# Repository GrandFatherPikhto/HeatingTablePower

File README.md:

# Reflow Oven & Heating Table Power Board (Dual Triac Switch)

*Читать на русском: [README_ru.md](README_ru.md)*

Hardware design (KiCad schematic and PCB layout) for the mains-side power board of the dual-channel reflow oven / heating table controller ([`../ControllerSTM32F103C8T6`](../ControllerSTM32F103C8T6)).

The board switches two resistive heaters from 220 V AC with **BTA12-600CRG** triacs. Each triac is driven through a **MOC3063M** zero-crossing optotriac, so the logic side is galvanically isolated from the mains.

---

## Key Features & Hardware Architecture

* **Two identical heater channels:** one hierarchical sheet (`channel.kicad_sch`) is placed twice, as `Channel 1` and `Channel 2`. Each channel has:
  * a BTA12-600CRG triac (`Q1` / `Q2`; 12 A RMS, 600 V, TO-220, insulated tab);
  * a MOC3063M optotriac (`U2` / `U3`) with a 330 Ω gate resistor (`R9` / `R12`, 1210);
  * an RC snubber across the triac: 39 Ω (`R10` / `R13`, axial) + 0.1 µF 630 V (`C7` / `C8`);
  * a heater output terminal (`J6` / `J7`).

  On the PCB, channel 2 is the channel 1 layout shifted 20 mm to the right.
* **Zero-cross switching:** the optotriacs turn the triacs on only near the mains zero crossing. This reduces inrush current and EMI. It also means the outputs suit on/off or burst-fire (whole half-cycle) control, not phase-angle dimming.
* **Logic input:** the control inputs come from `J4` and accept 3.3 V or 5 V logic. Each passes a 1 kΩ series resistor (`R3`, `R4`) into a Schmitt-trigger inverter `U1`, which must be a **74HCT14** (see note 5). Each input has a 10 kΩ pull-down (`R1`, `R2`), so a disconnected cable means "heater off".
* **Optotriac drive:** the LED of each MOC3063M is fed from `+5P` through 330 Ω (`R8`, `R11`) and is sunk by the `U1` output, giving ≈ 10–11 mA (the MOC3063M needs 5 mA max to trigger).
* **Status LEDs:** a second inverter of `U1` in each channel drives the channel LED, which is lit while the heater is on:
  * `D2` (purple, `R6`) — channel 1;
  * `D1` (blue, `R5`) — channel 2;
  * `D3` (red, `R7`) — logic power present.
* **Net ties `NT1` / `NT2`:** they split the thin optotriac branch (`UP_ARM`, 0.5 mm track) off the heavy heater net (`220V_UP`). The branch is therefore a separate net with its own width, and the mains-track rule in `Power.kicad_dru` does not apply to it.
* **Mains input protection:** varistor `RV1` (SIOV-S14K275, 275 V AC) and an across-the-line capacitor `C1` (0.1 µF 630 V). **There is no fuse on the board** — see the notes.
* **Logic supply filtering:** `C4` (47 µF 10 V), `C5` (10 µF) and `C6` (100 nF) at `J5`; `C2` (100 nF) and `C3` (10 µF) at `U1`.
* **Board:** 2 layers, ≈ 93 × 65 mm, 4× M3 mounting holes.

---

## Repository Structure

* `Power.kicad_pro` — KiCad project file.
* `Power.kicad_sch` — root schematic sheet. Its hierarchical sheets:
  * `signal.kicad_sch` (`Signal`) — `J4`, the input network, `U1` and the channel LEDs;
  * `power.kicad_sch` (`Power`) — `J5`, logic supply filtering and the power LED;
  * `220v_in.kicad_sch` (`220V`) — `J1`, `RV1`, `C1`;
  * `channel.kicad_sch` (`Channel 1`, `Channel 2`) — one heater channel.
* `Power.kicad_pcb` — PCB layout.
* `Power.kicad_dru` — Custom design rule: tracks of the mains nets (`*/220V*`) may have exposed copper (no solder mask) so they can be tinned for extra current capacity.
* `gerber/` — Gerber and drill files. They are dated 27.10 and belong to the previous, flat-schematic revision. Regenerate them before ordering.
* `out/` — BOM and netclass audit reports.

---

## Connector Pinouts

### J1 — Mains Input (`220V In`, Phoenix MKDS 1.5, 5.08 mm)

| Pin | Signal | Description |
| :---: | :--- | :--- |
| 1 | `/220V` | Goes to A1 of both triacs, the snubbers, `RV1` and `C1`. Connect **Line (L)** here. |
| 2 | `/220V_COMMON` | Goes straight to pin 2 of both heater terminals. Connect **Neutral (N)** here. |

### J4 — Heater Control Inputs (`Signal Input`, JST-XH 4-pin)

Pin-compatible with `J10 (Signal Out)` of the controller board (straight cable).

| Pin | Signal | Description |
| :---: | :--- | :--- |
| 1 | `GND` | Ground |
| 2 | `HEATER_IN_01` | Channel 1 control, active high (3.3 / 5 V logic) |
| 3 | `GND` | Ground |
| 4 | `HEATER_IN_02` | Channel 2 control, active high (3.3 / 5 V logic) |

### J5 — Logic Power Input (`+5V In`, JST-XH 2-pin)

| Pin | Signal | Description |
| :---: | :--- | :--- |
| 1 | `+5P` | +5 V supply for `U1`, the LEDs and the optotriac LEDs |
| 2 | `GND` | Ground (shared with the controller via `J4`) |

### J6 / J7 — Heater Outputs (`Heater Out`, Phoenix MKDS 1.5, 5.08 mm)

| Pin | Signal | Description |
| :---: | :--- | :--- |
| 1 | `220V_UP` | Switched output from the triac (A2) |
| 2 | `/220V_COMMON` | Heater common (Neutral) |

### Channel Map

The channels run straight through:

| Input (`J4`) | `U1` gates | Optotriac | Triac | Output | Status LED |
| :--- | :---: | :---: | :---: | :---: | :--- |
| `HEATER_IN_01` (pin 2) | 1→2, 13→12 | `U2` | `Q1` | `J6` | `D2` (purple) |
| `HEATER_IN_02` (pin 4) | 3→4, 11→10 | `U3` | `Q2` | `J7` | `D1` (blue) |

The unused inputs of `U1` (pins 5 and 9) are tied to `GND`.

---

## Assembly & Safety Notes

1. **Mains voltage.** All of the following are at mains potential: `J1`, `J6`, `J7`, the triacs, gate resistors `R9`/`R12`, the snubbers, `NT1`/`NT2`, `RV1`, `C1` and pins 4–6 of the optotriacs. Do not touch the board while it is plugged in.
2. **Fusing is external.** The board has no fuse. Install a fuse (or circuit breaker) in the Line wire **before** `J1`, rated for the total current of both heaters. The varistor `RV1` relies on that upstream fuse: when overloaded it fails short. Make sure the mains traces can carry the fuse rating.
3. **`C1` must be an X2 safety capacitor.** It sits directly across the line. X2 parts are also the safe choice for the snubber capacitors `C7`/`C8`. The footprints (10 mm pitch, MKS4-size) fit standard X2 film capacitors.
4. **Heatsinks.** A BTA12 dissipates roughly 1–1.5 W per ampere of heater current. Above ~2 A per channel, mount the triacs on a heatsink (the BTA tab is insulated, so both can share one).
5. **`U1` must be a 74HCT14.** The controller drives `J4` from a 74HC14 powered at 3.3 V, so a high level is about 3.3 V. The HCT input threshold is TTL-level (VIH = 2.0 V) and accepts it with margin. A plain 74HC14 at 5 V has its positive Schmitt threshold at up to ≈ 3.5 V and is not guaranteed to see 3.3 V as high.
6. **Fail-safe input.** The pull-downs `R1`/`R2` keep both heaters off when the cable is unplugged. On the controller side, the inputs of its `U6` are pulled down too, so the heaters also stay off while the STM32 is in reset or being flashed.

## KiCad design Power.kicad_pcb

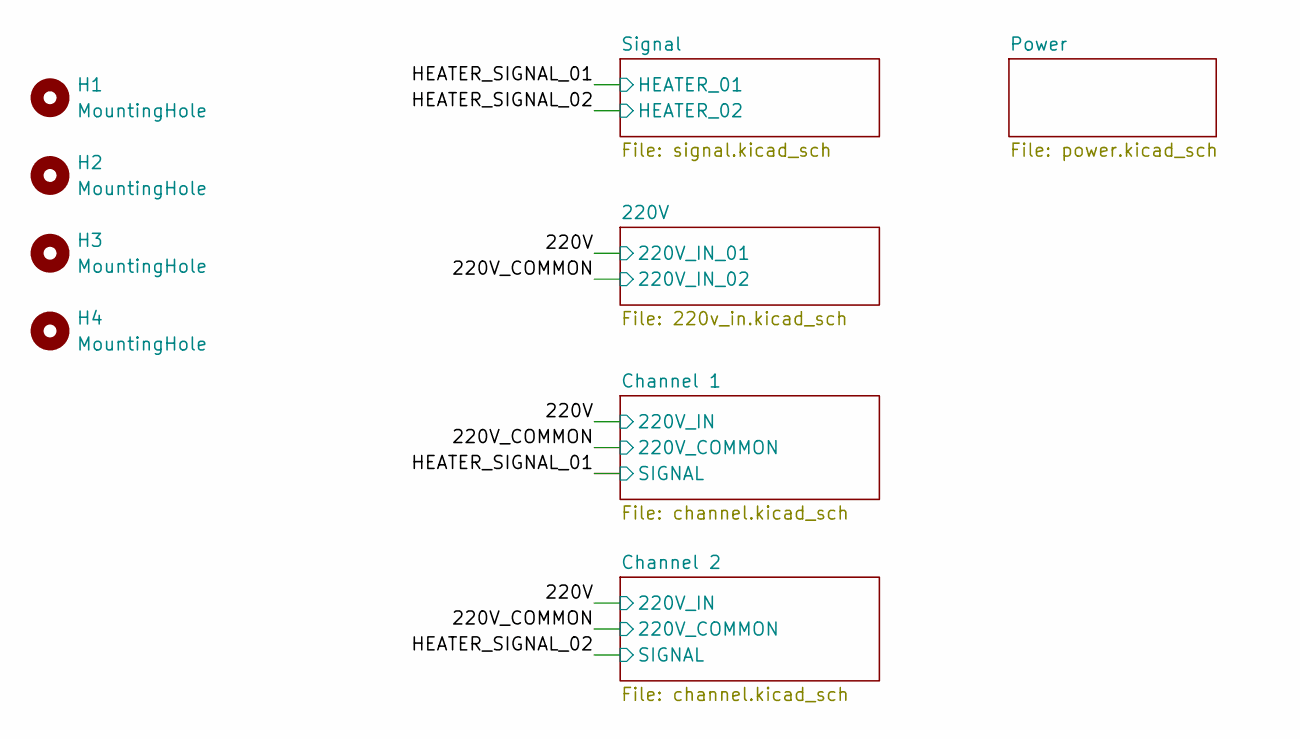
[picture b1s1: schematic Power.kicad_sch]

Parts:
H1, H2, H3, H4: MountingHole; MountingHole_3.2mm_M3

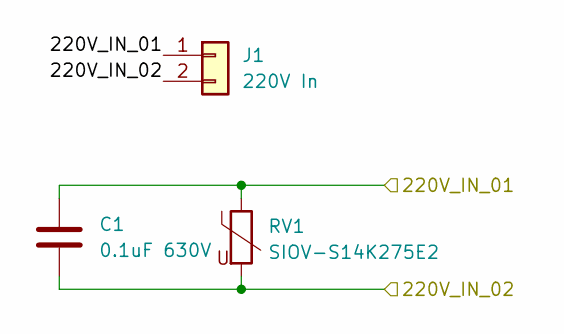
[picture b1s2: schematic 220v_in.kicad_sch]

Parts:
C1: 0.1uF 630V; C_Rect_L13.0mm_W6.0mm_P10.00mm_FKS3_FKP3_MKS4
J1: 220V In; TerminalBlock_Phoenix_MKDS-1,5-2-5.08_1x02_P5.08mm_Horizont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
RV1: SIOV-S14K275E2; RV_Disc_D15.5mm_W5mm_P7.5mm

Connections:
/220V: C1.1, J1.1, RV1.1; also elsewhere on the board
/220V_COMMON: C1.2, J1.2, RV1.2; also elsewhere on the board

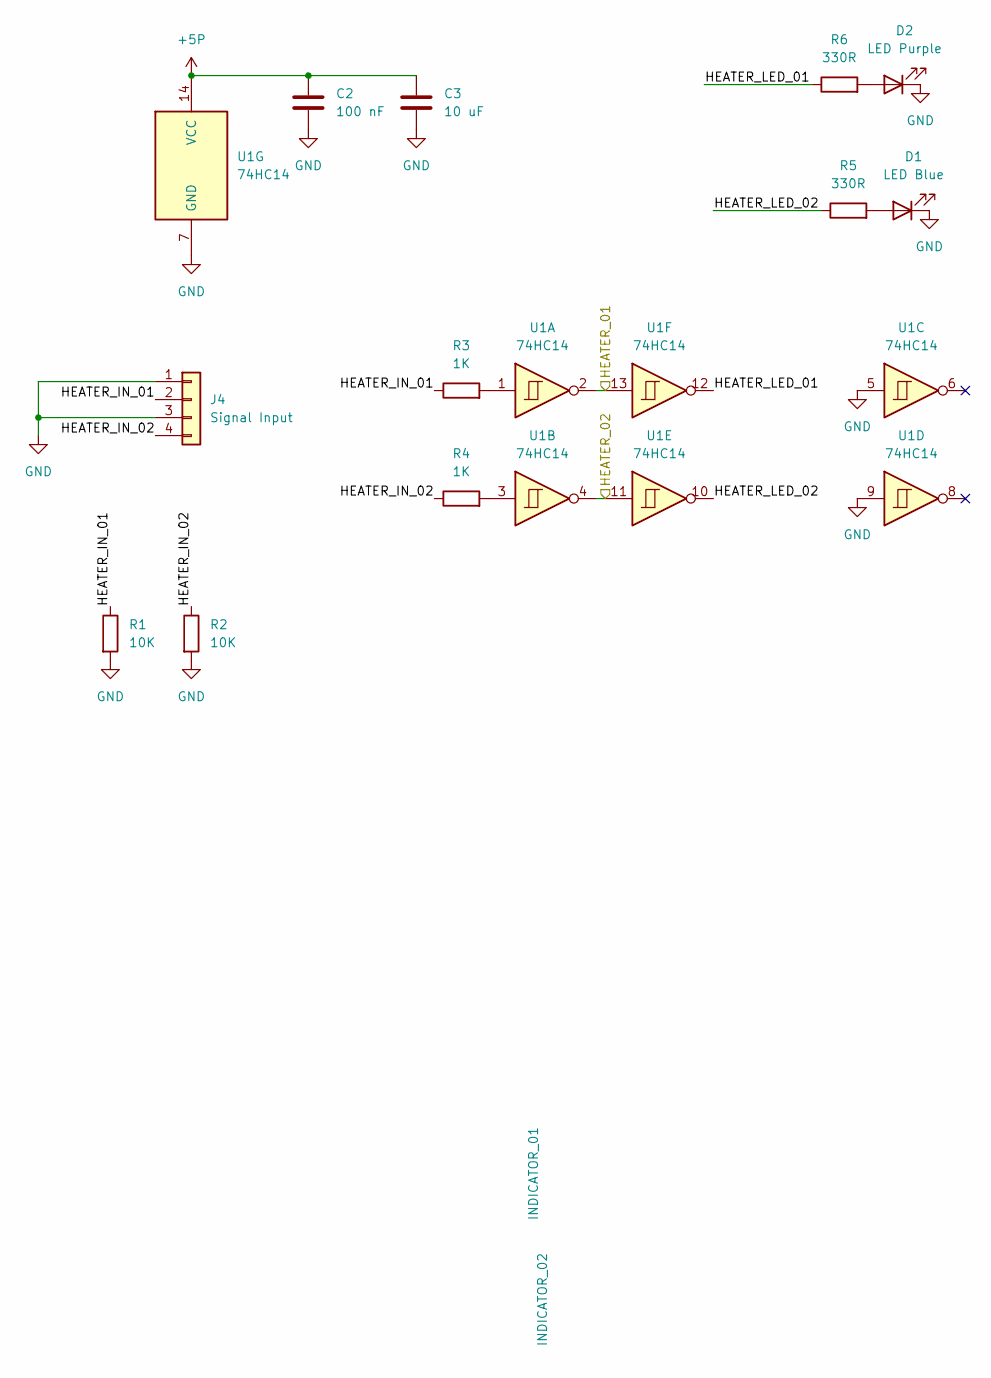
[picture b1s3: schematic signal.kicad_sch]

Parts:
C2: 100 nF; C_0402_1005Metric_Pad0.74x0.62mm_HandSolder
C3: 10 uF; C_0603_1608Metric_Pad1.08x0.95mm_HandSolder
D1: LED Blue; LED_0805_2012Metric_Pad1.15x1.40mm_HandSolder
D2: LED Purple; LED_0805_2012Metric_Pad1.15x1.40mm_HandSolder
J4: Signal Input; JST_XH_B4B-XH-A_1x04_P2.50mm_Vertical
R1, R2: 10K; R_0402_1005Metric_Pad0.72x0.64mm_HandSolder
R3, R4: 1K; R_0402_1005Metric_Pad0.72x0.64mm_HandSolder
R5, R6: 330R; R_0402_1005Metric_Pad0.72x0.64mm_HandSolder
U1: 74HC14; SOIC-14_3.9x8.7mm_P1.27mm

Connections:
+5P: C2.1, C3.1, U1.14 (VCC); also elsewhere on the board
/HEATER_SIGNAL_01: U1.2, U1.13; also elsewhere on the board
/HEATER_SIGNAL_02: U1.4, U1.11; also elsewhere on the board
/Signal/HEATER_IN_01: J4.2, R1.1, R3.1
/Signal/HEATER_IN_02: J4.4, R2.1, R4.1
/Signal/HEATER_LED_01: R6.1, U1.12
/Signal/HEATER_LED_02: R5.1, U1.10
GND: C2.2, C3.2, D1.1 (K), D2.1 (K), J4.1, J4.3, R1.2, R2.2, U1.5, U1.7 (GND), U1.9; also elsewhere on the board
unnamed: D1.2 (A), R5.2
unnamed: D2.2 (A), R6.2
unnamed: R3.2, U1.1
unnamed: R4.2, U1.3

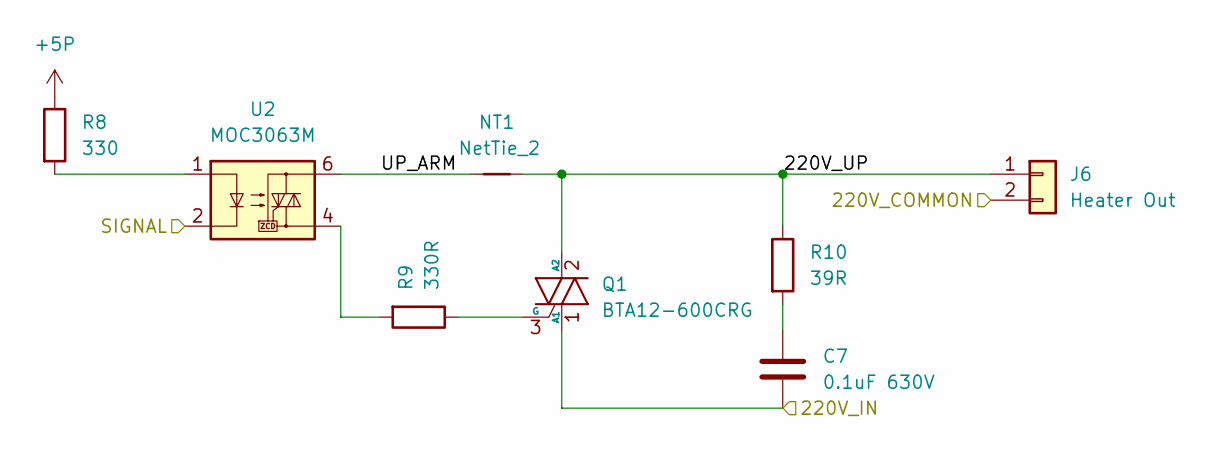
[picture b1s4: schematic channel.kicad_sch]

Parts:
C7: 0.1uF 630V; C_Rect_L13.0mm_W6.0mm_P10.00mm_FKS3_FKP3_MKS4
J6: Heater Out; TerminalBlock_Phoenix_MKDS-1,5-2-5.08_1x02_P5.08mm_Horizont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
NT1: NetTie_2; NetTie-2_SMD_Pad0.5mm
Q1: BTA12-600CRG; TO-220-3_Vertical
R8: 330; R_0402_1005Metric_Pad0.72x0.64mm_HandSolder
R9: 330R; R_1210_3225Metric_Pad1.30x2.65mm_HandSolder
R10: 39R; R_Axial_DIN0516_L15.5mm_D5.0mm_P20.32mm_Horizontal
U2: MOC3063M; DIP-6_W7.62mm

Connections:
+5P: R8.1; also elsewhere on the board
/220V: C7.2, Q1.1 (A1); also elsewhere on the board
/220V_COMMON: J6.2; also elsewhere on the board
/Channel 1/220V_UP: J6.1, NT1.2, Q1.2 (A2), R10.1
/Channel 1/UP_ARM: NT1.1, U2.6
/HEATER_SIGNAL_01: U2.2; also elsewhere on the board
unnamed: C7.1, R10.2
unnamed: Q1.3 (G), R9.1
unnamed: R8.2, U2.1
unnamed: R9.2, U2.4

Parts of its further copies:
C8: 0.1uF 630V; C_Rect_L13.0mm_W6.0mm_P10.00mm_FKS3_FKP3_MKS4
J7: Heater Out; TerminalBlock_Phoenix_MKDS-1,5-2-5.08_1x02_P5.08mm_Horizont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
NT2: NetTie_2; NetTie-2_SMD_Pad0.5mm
Q2: BTA12-600CRG; TO-220-3_Vertical
R11: 330; R_0402_1005Metric_Pad0.72x0.64mm_HandSolder
R12: 330R; R_1210_3225Metric_Pad1.30x2.65mm_HandSolder
R13: 39R; R_Axial_DIN0516_L15.5mm_D5.0mm_P20.32mm_Horizontal
U3: MOC3063M; DIP-6_W7.62mm

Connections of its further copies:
+5P: R11.1; also elsewhere on the board
/220V: C8.2, Q2.1 (A1); also elsewhere on the board
/220V_COMMON: J7.2; also elsewhere on the board
/Channel 2/220V_UP: J7.1, NT2.2, Q2.2 (A2), R13.1
/Channel 2/UP_ARM: NT2.1, U3.6
/HEATER_SIGNAL_02: U3.2; also elsewhere on the board
unnamed: C8.1, R13.2
unnamed: Q2.3 (G), R12.1
unnamed: R11.2, U3.1
unnamed: R12.2, U3.4

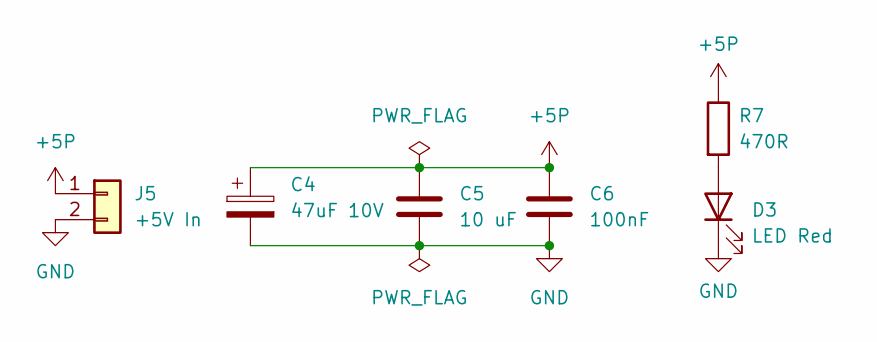
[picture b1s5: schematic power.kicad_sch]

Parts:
C4: 47uF 10V; CP_Radial_D5.0mm_P2.00mm
C5: 10 uF; C_0603_1608Metric_Pad1.08x0.95mm_HandSolder
C6: 100nF; C_0402_1005Metric_Pad0.74x0.62mm_HandSolder
D3: LED Red; LED_0805_2012Metric_Pad1.15x1.40mm_HandSolder
J5: +5V In; JST_XH_B2B-XH-A_1x02_P2.50mm_Vertical
R7: 470R; R_0402_1005Metric_Pad0.72x0.64mm_HandSolder

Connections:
+5P: C4.1, C5.1, C6.1, J5.1, R7.1; also elsewhere on the board
GND: C4.2, C5.2, C6.2, D3.1 (K), J5.2; also elsewhere on the board
unnamed: D3.2 (A), R7.2

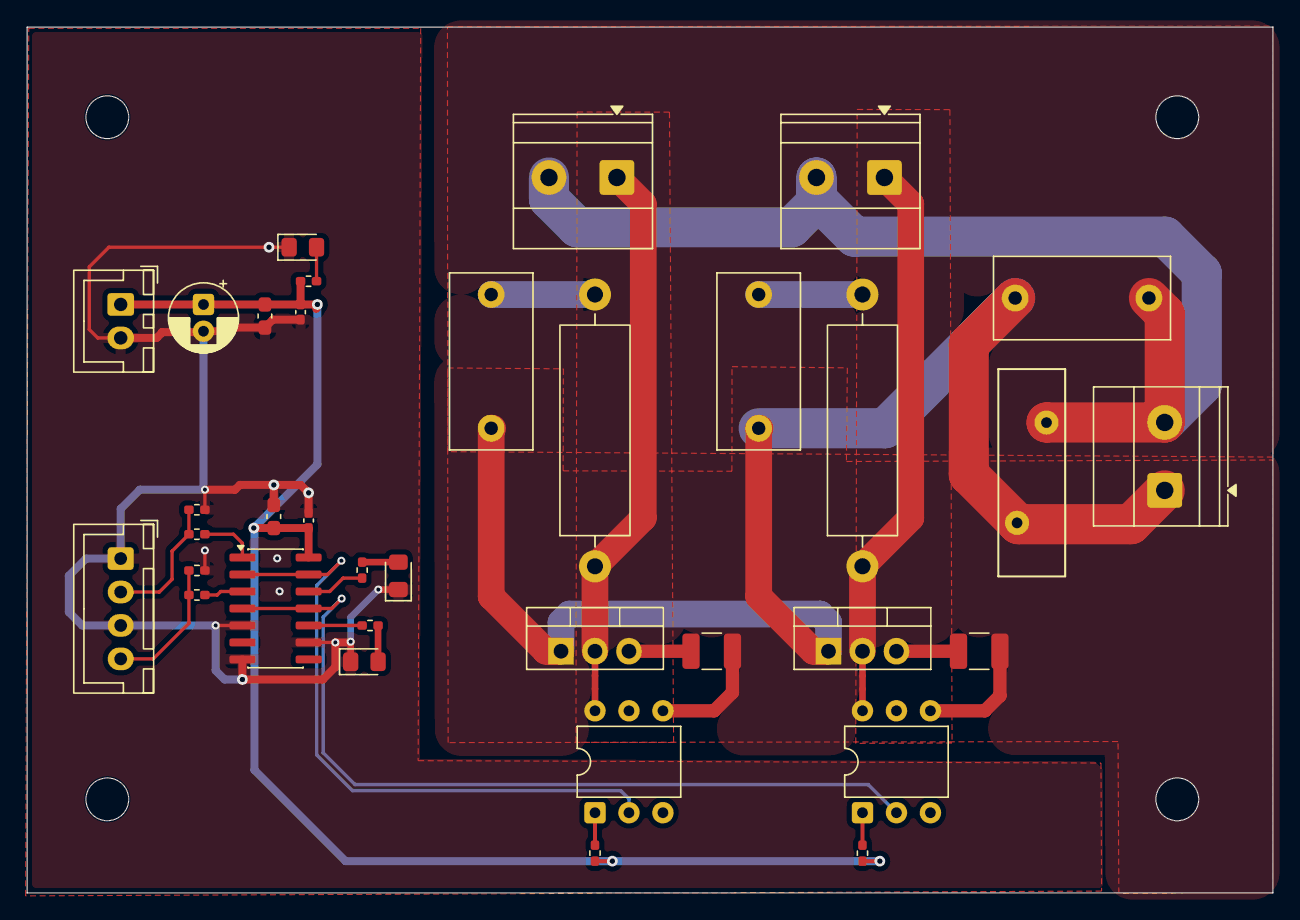
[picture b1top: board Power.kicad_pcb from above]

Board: 2 copper layers, 93.2 x 64.7 mm, 41 parts (0 on the bottom side), 27 nets.

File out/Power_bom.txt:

=== BOM (список компонентов) для Power.net ===

Компонент | Номинал                   | Footprint                     
----------------------------------------------------------------
C1   | 0.1uF 630V                | C_Rect_L13.0mm_W6.0mm_P10.00mm_FKS3_FKP3_MKS4
C2   | 100 nF                    | C_0402_1005Metric_Pad0.74x0.62mm_HandSolder
C3   | 10 uF                     | C_0603_1608Metric_Pad1.08x0.95mm_HandSolder
C4   | 47uF 10V                  | CP_Radial_D5.0mm_P2.00mm      
C5   | 10 uF                     | C_0603_1608Metric_Pad1.08x0.95mm_HandSolder
C6   | 100nF                     | C_0402_1005Metric_Pad0.74x0.62mm_HandSolder
C7   | 0.1uF 630V                | C_Rect_L13.0mm_W6.0mm_P10.00mm_FKS3_FKP3_MKS4
C8   | 0.1uF 630V                | C_Rect_L13.0mm_W6.0mm_P10.00mm_FKS3_FKP3_MKS4
D1   | LED Blue                  | LED_0805_2012Metric_Pad1.15x1.40mm_HandSolder
D2   | LED Purple                | LED_0805_2012Metric_Pad1.15x1.40mm_HandSolder
D3   | LED Red                   | LED_0805_2012Metric_Pad1.15x1.40mm_HandSolder
H1   | MountingHole              | MountingHole_3.2mm_M3         
H2   | MountingHole              | MountingHole_3.2mm_M3         
H3   | MountingHole              | MountingHole_3.2mm_M3         
H4   | MountingHole              | MountingHole_3.2mm_M3         
J1   | Heater 01                 | TerminalBlock_Phoenix_MKDS-1,5-2-5.08_1x02_P5.08mm_Horizontal
J4   | Signal Input              | JST_XH_B4B-XH-A_1x04_P2.50mm_Vertical
J5   | +5V In                    | JST_XH_B2B-XH-A_1x02_P2.50mm_Vertical
J6   | Heater Out                | TerminalBlock_Phoenix_MKDS-1,5-2-5.08_1x02_P5.08mm_Horizontal
J7   | Heater Out                | TerminalBlock_Phoenix_MKDS-1,5-2-5.08_1x02_P5.08mm_Horizontal
NT1  | NetTie_2                  | NetTie-2_SMD_Pad0.5mm         
NT2  | NetTie_2                  | NetTie-2_SMD_Pad0.5mm         
Q1   | BTA12-600CRG              | TO-220-3_Vertical             
Q2   | BTA12-600CRG              | TO-220-3_Vertical             
R1   | 10K                       | R_0402_1005Metric_Pad0.72x0.64mm_HandSolder
R2   | 10K                       | R_0402_1005Metric_Pad0.72x0.64mm_HandSolder
R3   | 1K                        | R_0402_1005Metric_Pad0.72x0.64mm_HandSolder
R4   | 1K                        | R_0402_1005Metric_Pad0.72x0.64mm_HandSolder
R5   | 330R                      | R_0402_1005Metric_Pad0.72x0.64mm_HandSolder
R6   | 330R                      | R_0402_1005Metric_Pad0.72x0.64mm_HandSolder
R7   | 470R                      | R_0402_1005Metric_Pad0.72x0.64mm_HandSolder
R8   | 330                       | R_0402_1005Metric_Pad0.72x0.64mm_HandSolder
R9   | 330R                      | R_1210_3225Metric_Pad1.30x2.65mm_HandSolder
R10  | 39R                       | R_Axial_DIN0516_L15.5mm_D5.0mm_P20.32mm_Horizontal
R11  | 330                       | R_0402_1005Metric_Pad0.72x0.64mm_HandSolder
R12  | 330R                      | R_1210_3225Metric_Pad1.30x2.65mm_HandSolder
R13  | 39R                       | R_Axial_DIN0516_L15.5mm_D5.0mm_P20.32mm_Horizontal
RV1  | SIOV-S14K275E2            | RV_Disc_D15.5mm_W5mm_P7.5mm   
U1   | 74HC14                    | SOIC-14_3.9x8.7mm_P1.27mm     
U2   | MOC3063M                  | DIP-6_W7.62mm                 
U3   | MOC3063M                  | DIP-6_W7.62mm
